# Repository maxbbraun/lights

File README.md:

# Lights

Design and source code for controlling a ring of LEDs via Bluetooth LE. More context for the project [here](https://medium.com/@maxbraun/smarter-mirrors-and-how-theyre-made-327997b9eff7).

## Eagle

The light ring PCB design is defined in an [Eagle project](eagle) ready for fabrication. It uses [APA102 5050 RGB LEDs](https://www.adafruit.com/product/2343).

## Arduino

The PCB (5V) is connected to an [Adafruit Feather with BLE](https://www.adafruit.com/product/2829) (3.3V) with a [logic level converter](https://www.adafruit.com/product/757). After [board setup](https://learn.adafruit.com/adafruit-feather-32u4-bluefruit-le/setup) select `Adafruit Feather 32u4` as the board and `USBtinyISP` as the programmer.

The [Arduino code](arduino/lights.ino) contains the [pin definitions](arduino/lights.ino#L19) and has three library dependencies:
* [APA102](https://github.com/pololu/apa102-arduino#software)
* [Adafruit Bluefruit LE](https://github.com/adafruit/Adafruit_BluefruitLE_nRF51)
* [FastGPIO](https://github.com/pololu/fastgpio-arduino)

## Android

The [Android Studio project](android) builds an apk with a background service maintaining the BLE connection.

Bind to the service from another app and send commands using the [AIDL](android/app/src/main/aidl/net/maxbraun/lights) interface.

You can also use the [debug UI](android/app/src/main/java/net/maxbraun/lights/DebugActivity.java) or send intents to the [debug service](android/app/src/main/java/net/maxbraun/lights/DebugService.java):

```
adb shell am startservice net.maxbraun.lights/.DebugService
adb shell am broadcast -a net.maxbraun.lights.ALL_WHITE
```

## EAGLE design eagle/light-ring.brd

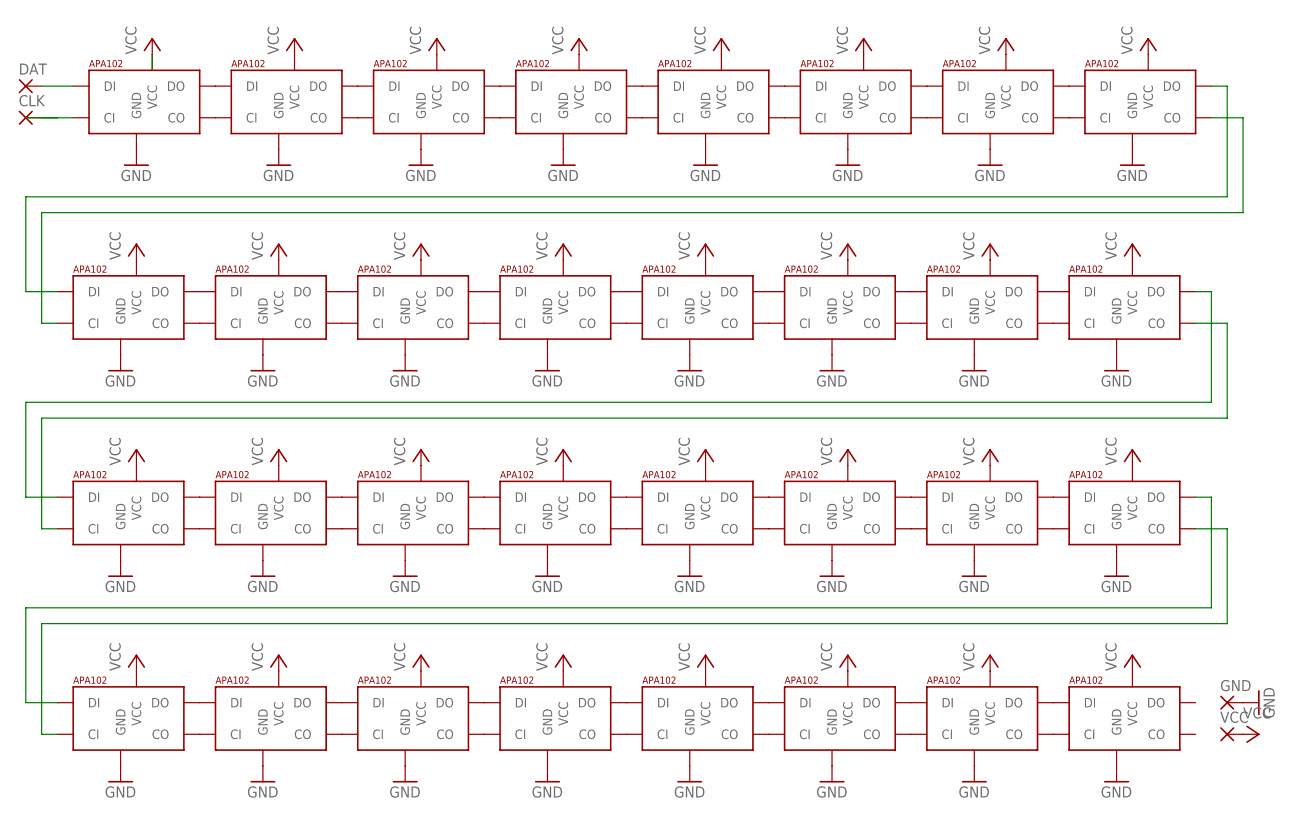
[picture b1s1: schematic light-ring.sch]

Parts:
CLK: 2,15/1,0
DAT: 2,15/1,0
GND: 2,15/1,0
LED_1, LED_2, LED_3, LED_4, LED_5, LED_6, LED_7, LED_8, LED_9, LED_10, LED_11, LED_12, LED_13, LED_14, LED_15, LED_16, LED_17, LED_18, LED_19, LED_20, LED_21, LED_22, LED_23, LED_24, LED_25, LED_26, LED_27, LED_28, LED_29, LED_30, LED_31, LED_32: APA1025050; APA102_5050
VCC: 2,15/1,0

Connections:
CLK_IN: CLK.1, LED_1.5 (CI)
DAT_IN: DAT.1, LED_1.4 (DI)
GND: GND.1, LED_1.6 (GND), LED_2.6 (GND), LED_3.6 (GND), LED_4.6 (GND), LED_5.6 (GND), LED_6.6 (GND), LED_7.6 (GND), LED_8.6 (GND), LED_9.6 (GND), LED_10.6 (GND), LED_11.6 (GND), LED_12.6 (GND), LED_13.6 (GND), LED_14.6 (GND), LED_15.6 (GND), LED_16.6 (GND), LED_17.6 (GND), LED_18.6 (GND), LED_19.6 (GND), LED_20.6 (GND), LED_21.6 (GND), LED_22.6 (GND), LED_23.6 (GND), LED_24.6 (GND), LED_25.6 (GND), LED_26.6 (GND), LED_27.6 (GND), LED_28.6 (GND), LED_29.6 (GND), LED_30.6 (GND), LED_31.6 (GND), LED_32.6 (GND)
unnamed: LED_1.3 (DO), LED_2.4 (DI)
unnamed: LED_1.2 (CO), LED_2.5 (CI)
unnamed: LED_2.3 (DO), LED_3.4 (DI)
unnamed: LED_2.2 (CO), LED_3.5 (CI)
unnamed: LED_3.3 (DO), LED_4.4 (DI)
unnamed: LED_3.2 (CO), LED_4.5 (CI)
unnamed: LED_4.3 (DO), LED_5.4 (DI)
unnamed: LED_4.2 (CO), LED_5.5 (CI)
unnamed: LED_5.3 (DO), LED_6.4 (DI)
unnamed: LED_5.2 (CO), LED_6.5 (CI)
unnamed: LED_6.3 (DO), LED_7.4 (DI)
unnamed: LED_6.2 (CO), LED_7.5 (CI)
unnamed: LED_7.3 (DO), LED_8.4 (DI)
unnamed: LED_7.2 (CO), LED_8.5 (CI)
unnamed: LED_8.3 (DO), LED_9.4 (DI)
unnamed: LED_8.2 (CO), LED_9.5 (CI)
unnamed: LED_9.2 (CO), LED_10.5 (CI)
unnamed: LED_9.3 (DO), LED_10.4 (DI)
unnamed: LED_10.2 (CO), LED_11.5 (CI)
unnamed: LED_10.3 (DO), LED_11.4 (DI)
unnamed: LED_11.2 (CO), LED_12.5 (CI)
unnamed: LED_11.3 (DO), LED_12.4 (DI)
unnamed: LED_12.2 (CO), LED_13.5 (CI)
unnamed: LED_12.3 (DO), LED_13.4 (DI)
unnamed: LED_13.2 (CO), LED_14.5 (CI)
unnamed: LED_13.3 (DO), LED_14.4 (DI)
unnamed: LED_14.2 (CO), LED_15.5 (CI)
unnamed: LED_14.3 (DO), LED_15.4 (DI)
unnamed: LED_15.2 (CO), LED_16.5 (CI)
unnamed: LED_15.3 (DO), LED_16.4 (DI)
unnamed: LED_17.2 (CO), LED_18.5 (CI)
unnamed: LED_17.3 (DO), LED_18.4 (DI)
unnamed: LED_18.2 (CO), LED_19.5 (CI)
unnamed: LED_18.3 (DO), LED_19.4 (DI)
unnamed: LED_19.2 (CO), LED_20.5 (CI)
unnamed: LED_19.3 (DO), LED_20.4 (DI)
unnamed: LED_20.2 (CO), LED_21.5 (CI)
unnamed: LED_20.3 (DO), LED_21.4 (DI)
unnamed: LED_21.2 (CO), LED_22.5 (CI)
unnamed: LED_21.3 (DO), LED_22.4 (DI)
unnamed: LED_22.2 (CO), LED_23.5 (CI)
unnamed: LED_22.3 (DO), LED_23.4 (DI)
unnamed: LED_23.2 (CO), LED_24.5 (CI)
unnamed: LED_23.3 (DO), LED_24.4 (DI)
unnamed: LED_25.2 (CO), LED_26.5 (CI)
unnamed: LED_25.3 (DO), LED_26.4 (DI)
unnamed: LED_26.2 (CO), LED_27.5 (CI)
unnamed: LED_26.3 (DO), LED_27.4 (DI)
unnamed: LED_27.2 (CO), LED_28.5 (CI)
unnamed: LED_27.3 (DO), LED_28.4 (DI)
unnamed: LED_28.2 (CO), LED_29.5 (CI)
unnamed: LED_28.3 (DO), LED_29.4 (DI)
unnamed: LED_29.2 (CO), LED_30.5 (CI)
unnamed: LED_29.3 (DO), LED_30.4 (DI)
unnamed: LED_30.2 (CO), LED_31.5 (CI)
unnamed: LED_30.3 (DO), LED_31.4 (DI)
unnamed: LED_31.2 (CO), LED_32.5 (CI)
unnamed: LED_31.3 (DO), LED_32.4 (DI)
unnamed: LED_16.3 (DO), LED_17.4 (DI)
unnamed: LED_16.2 (CO), LED_17.5 (CI)
unnamed: LED_24.3 (DO), LED_25.4 (DI)
unnamed: LED_24.2 (CO), LED_25.5 (CI)
VCC: LED_1.1 (VCC), LED_2.1 (VCC), LED_3.1 (VCC), LED_4.1 (VCC), LED_5.1 (VCC), LED_6.1 (VCC), LED_7.1 (VCC), LED_8.1 (VCC), LED_9.1 (VCC), LED_10.1 (VCC), LED_11.1 (VCC), LED_12.1 (VCC), LED_13.1 (VCC), LED_14.1 (VCC), LED_15.1 (VCC), LED_16.1 (VCC), LED_17.1 (VCC), LED_18.1 (VCC), LED_19.1 (VCC), LED_20.1 (VCC), LED_21.1 (VCC), LED_22.1 (VCC), LED_23.1 (VCC), LED_24.1 (VCC), LED_25.1 (VCC), LED_26.1 (VCC), LED_27.1 (VCC), LED_28.1 (VCC), LED_29.1 (VCC), LED_30.1 (VCC), LED_31.1 (VCC), LED_32.1 (VCC), VCC.1

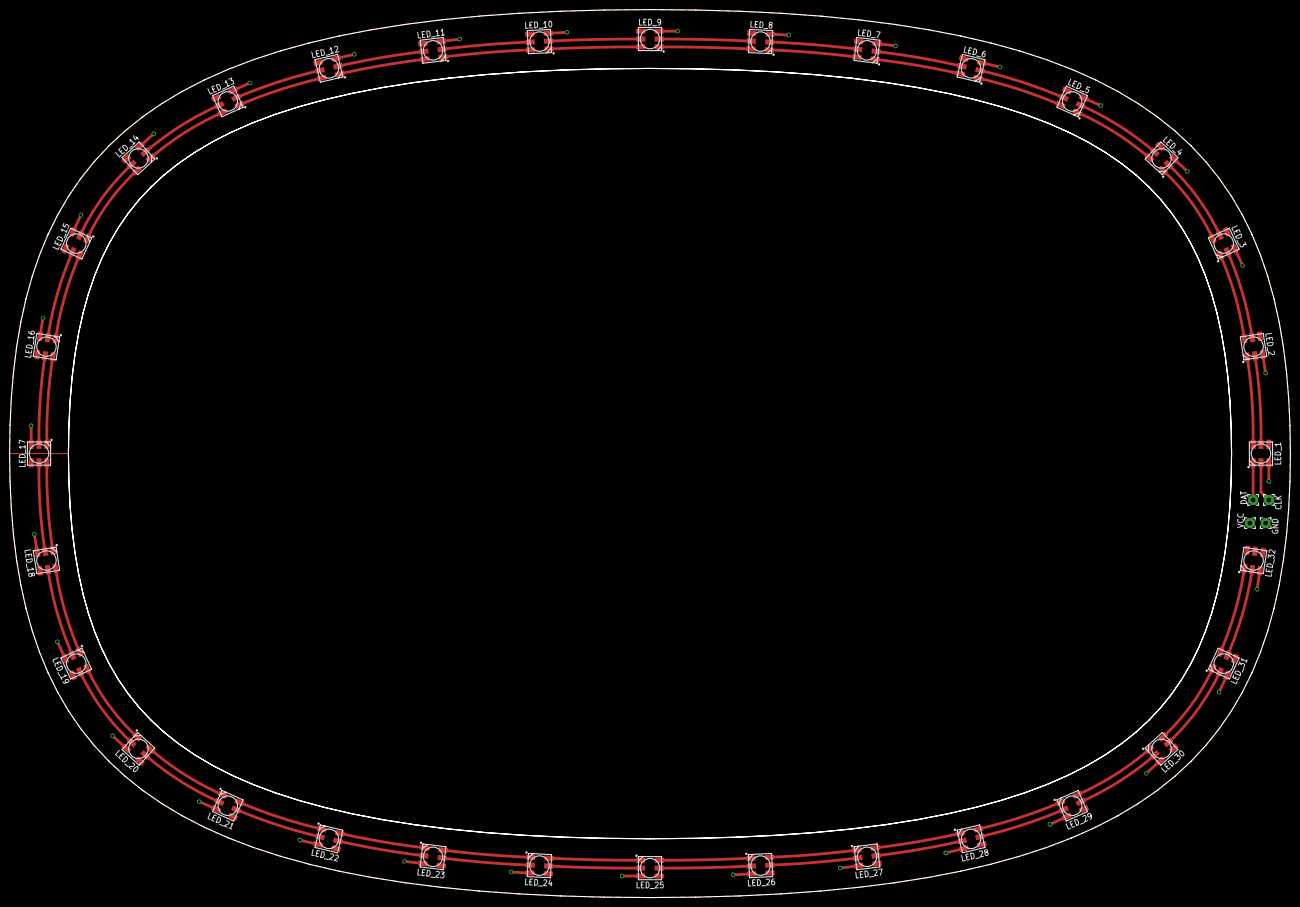
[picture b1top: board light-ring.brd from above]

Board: 2 copper layers, 276.5 x 191.7 mm, 36 parts (0 on the bottom side), 66 nets.

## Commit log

2017-07-23 First prototype
2017-11-05 Add Arduino source code
2017-11-06 Add Arduino instructions
2017-11-06 More details for Arduino instructions
2018-04-30 Update dependencies and clean up unused files
2018-05-13 Split into android and arduino directories
2018-05-13 Add eagle project
2018-05-13 Minor README edits
2018-05-13 Add license to README
2018-05-20 Fix typo
2018-05-28 Add images to README
2018-05-28 Add more details to README
2018-05-28 Fix broken link in README
2018-05-28 Add LED info to README
2018-05-28 Add PCB image
2018-05-28 Add more images
2018-05-28 Use mirror GIF instead of image
2018-05-28 Update images in README
2018-05-28 Add Medium link to README text
2020-06-04 Replace Apache License with MIT License
